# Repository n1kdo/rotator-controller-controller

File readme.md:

# Raspberry Pi Pico W IOT Antenna Rotator Controller Controller

This project uses a Raspberry Pi Pico W to internet-enable one or two antenna 
rotator controllers that have an RS-232 interface.  The software presents a web interface 
to the rotator, and also allows direct network control by N1MM+ and other software.

I used it for my Hy-Gain Ham IV rotator.  My Hy-Gain rotator control box has been modified to allow computer
control with the addition of a Ham Supply/Idiom Press *Rotor-EZ* module.  I further modified the rotator
control box to provide +5 Volts on Pin 1 (carrier detect) of the DE-9S RS-232 interface.  This allows the 
Raspberry Pi Pico W to rob power from the rotator control box.

See the [Documentation](documentation.md) for details.

There is very little external hardware required.  The most important other piece is a MAX3232 3.3 volt 
RS-232 level converter.  The MAX3232 is used to interface the 3.3 volt logic of the Raspberry Pi Pico W to
the RS-232 levels required by the antenna rotator control box.

## Installing MicroPython on your Pico-W

1. Download the latest stable build of [Pico W MicroPython](https://micropython.org/download/RPI_PICO_W/). 
   [This is the direct link](https://www.micropython.org/resources/firmware/RPI_PICO_W-20260824-v1.29.0.uf2).
2. Connect a micro-USB cable to your PC.  Hold down the white "BOOTSEL" button on the Pico-W, and insert the
   micro-USB cable into your Pico-W.
3. The Pico-W should appear as a USB storage device on your computer.  On mine, it shows up as "RPI-RP2 (F:)".
4. Copy/Paste the MicroPython .uf2 file to this drive.
5. Disconnect the Pico-W and prepare for the next step.

## Installing this software onto the Pico-W

The easiest way to get this software installed onto your Pico-W is to use the `loader.py` tool, also
provided in this repository.

1. Download Python 3 from https://www.python.org/downloads/ and install it.  Make sure to select "Add 
   Python 3 to Path."
2. Download the contents of this GitHub repository as a zip.  Use this URL: 
   `https://github.com/n1kdo/rotator-controller-controller/archive/refs/heads/master.zip`
3. Unpack that zip file somewhere. 
4. Open a command prompt.  (your choice.  Could be PowerShell, could be good ole CMD.)
5. From the command line, execute the following command: `pip install pyserial` -- this will install the Python 
   serial port support/
6. Change directory to where you unpacked the GitHub zip file, and then
   change directory to the `src/loader` directory.
7. From the command line, execute the following command: `python loader.py` -- this will install all the rotator
   controller-controller software onto the Pico-W.

If you want to experiment, you can use the open-source "Thonny" IDE to load the python source code and HTML files
onto the Pico W.  Unfortunately, Thonny cannot load the binary file `compass-background.png` image file into the
proper location, but this can be worked around by using the "upload" feature in the controller-controller software.

## What is all this stuff?

Important files:

* src/rotator/main.py -- the main Python application
* src/rotator/dcu1_rotator.py -- a Python module that queries and commands the rotator controller
* src/rotator/http_server.py -- a Python module that implements the web server
* src/rotator/morse_code.py -- a Python module that implements the morse code sender
* src/rotator/n1mm_udp.py -- a Python module that implements UDP send/receive to/from N1MM+
* src/rotator/content/rotator.html -- the rotator control web page
* src/rotator/content/setup.html -- the setup web page
* src/rotator/content/files.html -- the file upload/download web page
* src/rotator/data/config.json -- the configuration file.  automatically generated on first use if not present.

Other Stuff:

* src/loader/loader.py -- small Python application installs the six files above onto the Pico-W
* src/loader/pyboard.py -- patched pyboard library from Micropython. Patched to work on Pico-W.

Electronic Design Files:

* kicad/* -- Kicad 6 design files for schematic and PCB.

## Other projects using this technology

I used this same electronic design, and a lot of the same source code to make
the [KPA-500 IOT Thing](https://github.com/n1kdo/KPA500-remote), a web interface and 
KPA500-remote *host* for the Elecraft KPA-500 amplifier.

## Yes it works with N1MM+

See [Using the Rotator Controller-Controller with N1MM+](N1MM.md)

n1kdo 2026-09-21

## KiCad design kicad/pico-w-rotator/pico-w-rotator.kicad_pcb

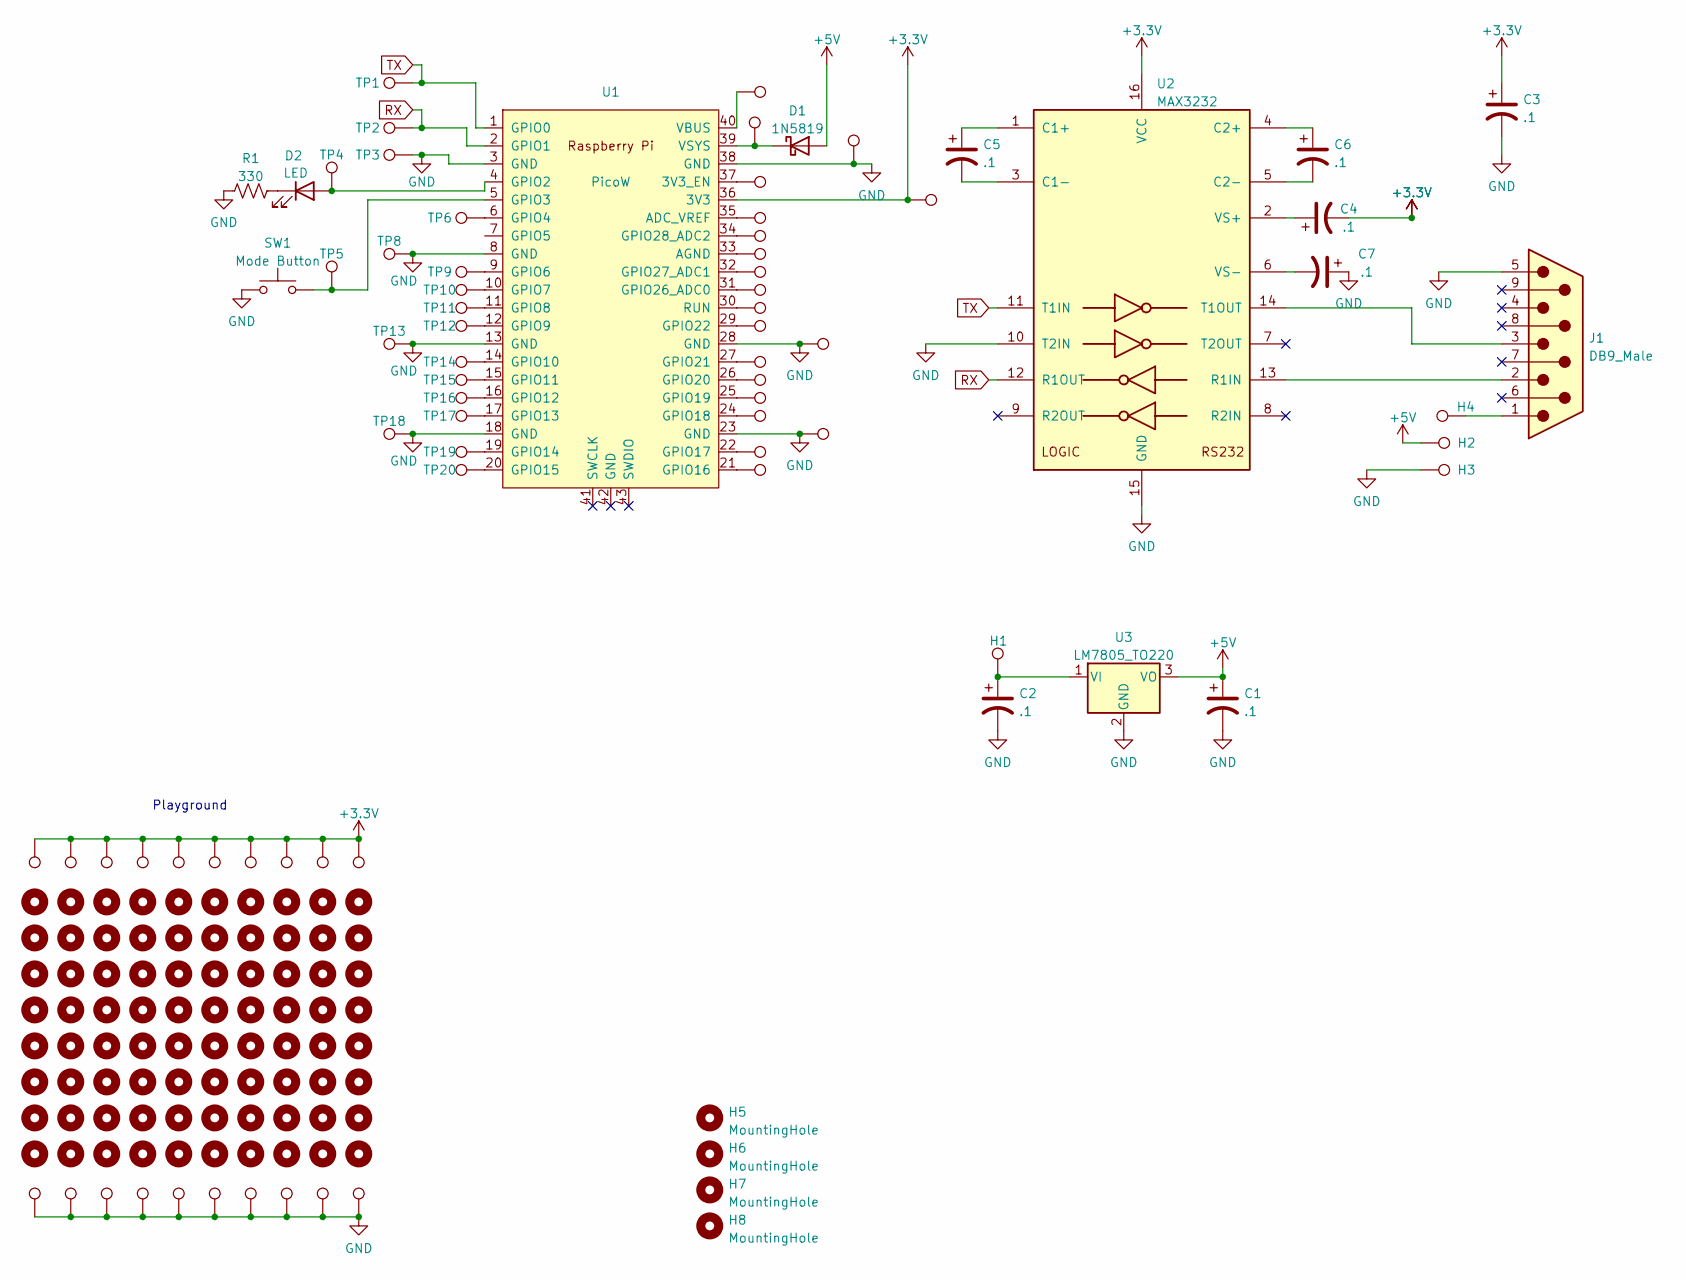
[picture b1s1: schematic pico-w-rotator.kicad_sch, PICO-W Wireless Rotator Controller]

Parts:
C1, C2, C3, C4, C5, C6, C7: .1; CP_Radial_Tantal_D4.5mm_P2.50mm; part T350A104M035AT
D1: 1N5819; D_DO-41_SOD81_P7.62mm_Horizontal
D2: LED; LED_D3.0mm
GH1, GH2, GH3, GH4, GH5, GH6, GH7, GH8, GH9, GH10, GH11, GH12, GH13, GH14, GH15, GH16, GH17, GH18, GH19, GH20, GH21, GH22, GH23, GH24, GH25, GH26, GH27, GH28, GH29, GH30, GH31, GH32, GH33, GH34, GH35, GH36, GH37, GH38, GH39, GH40, GH41, GH42, GH43, GH44, GH45, GH46, GH47, GH48, GH49, GH50, GH51, GH52, GH53, GH54, GH55, GH56, GH57, GH58, GH59, GH60, GH61, GH62, GH63, GH64, GH65, GH66, GH67, GH68, GH69, GH70, GH71, GH72, GH73, GH74, GH75, GH76, GH77, GH78, GH79, GH80, GH81, GH82, GH83, GH84, GH85, GH86, GH87, GH88, GH89, GH90, GH91, GH92, GH93, GH94, GH95, GH96, GH97, GH98, GH99, GH100: MountingHole; TestPoint_THTPad_D1.0mm_Drill0.5mm
H1, H3: 3; TestPoint_THTPad_D1.0mm_Drill0.5mm
H2: 2; TestPoint_THTPad_D1.0mm_Drill0.5mm
H4: 1; TestPoint_THTPad_D1.0mm_Drill0.5mm
H5, H6, H7, H8: MountingHole; MountingHole_3.5mm
J1: DB9_Male; DSUB-9_Male_Horizontal_P2.77x2.84mm_EdgePinOffset4.94mm_Hou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; part L717SDE09PA4CH4RC309
R1: 330; R_Axial_DIN0207_L6.3mm_D2.5mm_P7.62mm_Horizontal
SW1: Mode Button; GB215AHB; part GB215AH
TP1, TP2, TP3, TP4, TP5, TP6, TP8, TP9, TP10, TP11, TP12, TP13, TP14, TP15, TP16, TP17, TP18, TP19, TP20, TP21, TP22, TP23, TP24, TP25, TP26, TP27, TP28, TP29, TP30, TP31, TP32, TP33, TP34, TP35, TP36, TP37, TP38, TP39, TP40: TestPoint; TestPoint_THTPad_D1.0mm_Drill0.5mm
U1: PicoW; RPi_PicoW_SMD_TH
U2: MAX3232; DIP-16_W7.62mm_Socket
U3: LM7805_TO220; TO-220-3_Vertical

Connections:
+3.3V: C3.1, C4.2, GH1.1, GH11.1, GH21.1, GH31.1, GH41.1, GH51.1, GH61.1, GH71.1, GH81.1, GH91.1, TP36.1, U1.36 (3V3), U2.16 (VCC)
+5V: C1.1, D1.2 (A), H2.1, U3.3 (VO)
GND: C1.2, C2.2, C3.2, C7.1, GH10.1, GH20.1, GH30.1, GH40.1, GH50.1, GH60.1, GH70.1, GH80.1, GH90.1, GH100.1, H3.1, J1.5, R1.1, SW1.1, TP3.1, TP8.1, TP13.1, TP18.1, TP23.1, TP28.1, TP38.1, U1.3 (GND), U1.8 (GND), U1.13 (GND), U1.18 (GND), U1.23 (GND), U1.28 (GND), U1.38 (GND), U2.10 (T2IN), U2.15 (GND), U3.2 (GND)
unnamed: C2.1, H1.1, U3.1 (VI)
unnamed: C4.1, U2.2 (VS+)
unnamed: C5.1, U2.1 (C1+)
unnamed: C5.2, U2.3 (C1-)
unnamed: C6.1, U2.4 (C2+)
unnamed: C6.2, U2.5 (C2-)
unnamed: C7.2, U2.6 (VS-)
unnamed: D1.1 (K), TP39.1, U1.39 (VSYS)
unnamed: D2.1 (K), R1.2
unnamed: D2.2 (A), TP4.1, U1.4 (GPIO2)
unnamed: H4.1, J1.1
unnamed: J1.2, U2.13 (R1IN)
unnamed: J1.3, U2.14 (T1OUT)
unnamed: SW1.2, TP5.1, U1.5 (GPIO3)
unnamed: TP6.1, U1.6 (GPIO4)
unnamed 18: U1.7 (GPIO5); also elsewhere on the board
unnamed: TP9.1, U1.9 (GPIO6)
unnamed: TP10.1, U1.10 (GPIO7)
unnamed: TP11.1, U1.11 (GPIO8)
unnamed: TP12.1, U1.12 (GPIO9)
unnamed: TP14.1, U1.14 (GPIO10)
unnamed: TP15.1, U1.15 (GPIO11)
unnamed: TP16.1, U1.16 (GPIO12)
unnamed: TP17.1, U1.17 (GPIO13)
unnamed: TP19.1, U1.19 (GPIO14)
unnamed: TP20.1, U1.20 (GPIO15)
unnamed: TP21.1, U1.21 (GPIO16)
unnamed: TP22.1, U1.22 (GPIO17)
unnamed: TP24.1, U1.24 (GPIO18)
unnamed: TP25.1, U1.25 (GPIO19)
unnamed: TP26.1, U1.26 (GPIO20)
unnamed: TP27.1, U1.27 (GPIO21)
unnamed: TP29.1, U1.29 (GPIO22)
unnamed: TP30.1, U1.30 (RUN)
unnamed: TP31.1, U1.31 (GPIO26_ADC0)
unnamed: TP32.1, U1.32 (GPIO27_ADC1)
unnamed: TP33.1, U1.33 (AGND)
unnamed: TP34.1, U1.34 (GPIO28_ADC2)
unnamed: TP35.1, U1.35 (ADC_VREF)
unnamed: TP37.1, U1.37 (3V3_EN)
unnamed: TP40.1, U1.40 (VBUS)
RX: TP2.1, U1.2 (GPIO1), U2.12 (R1OUT)
TX: TP1.1, U1.1 (GPIO0), U2.11 (T1IN)

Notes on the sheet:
Playground

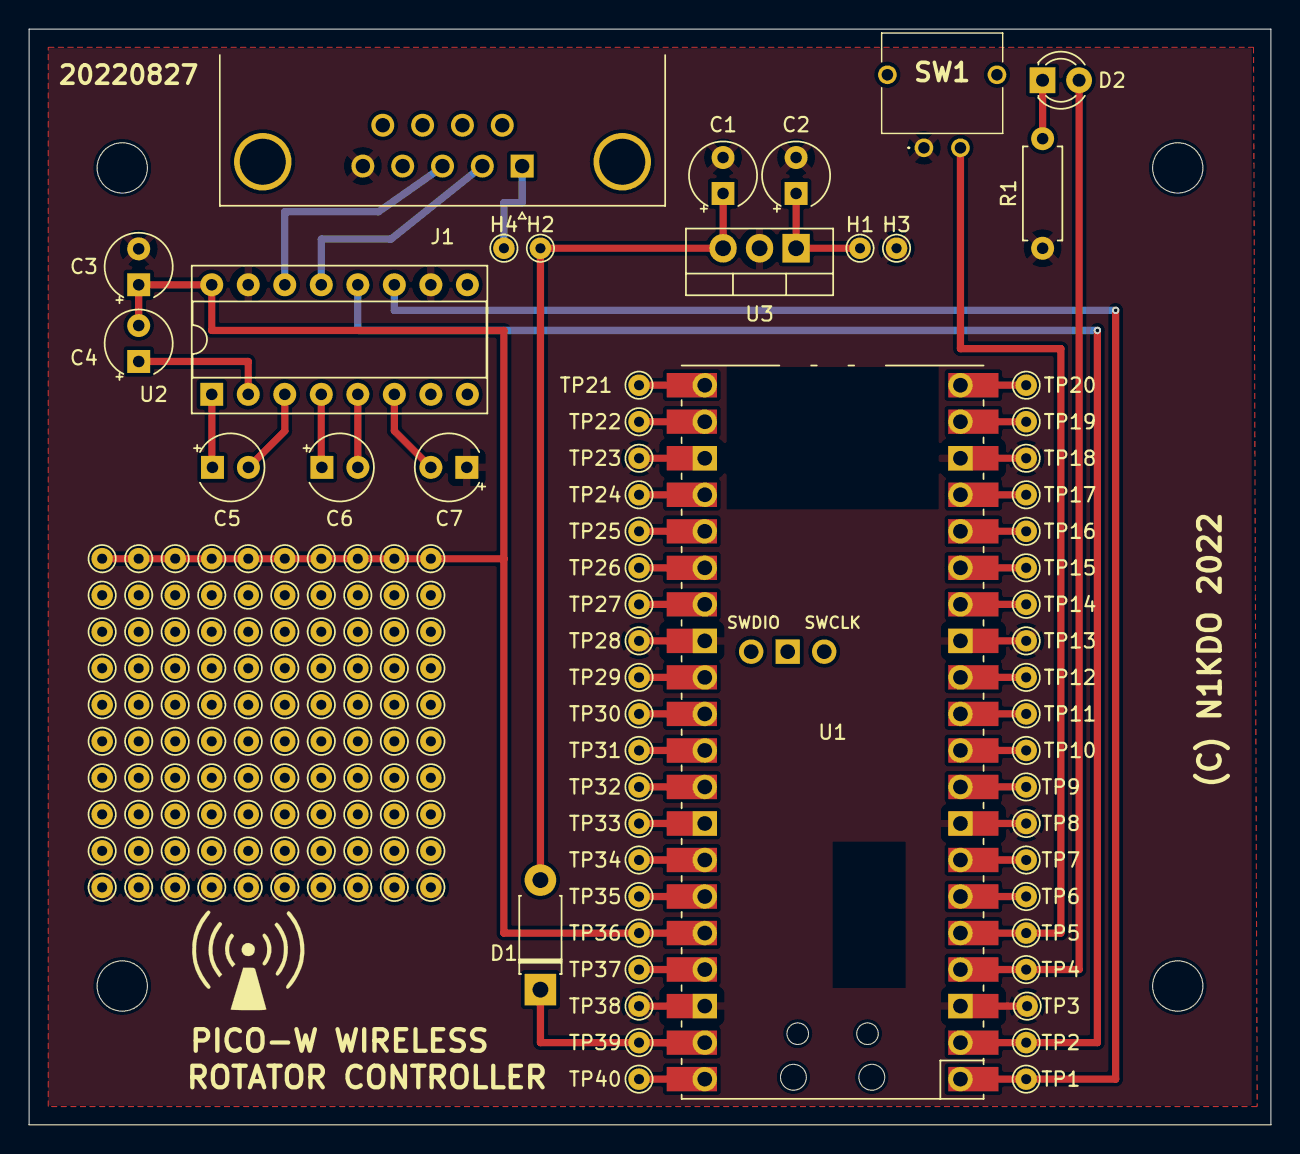
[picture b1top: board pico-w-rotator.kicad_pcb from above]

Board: 2 copper layers, 86.4 x 76.2 mm, 164 parts (0 on the bottom side), 46 nets.

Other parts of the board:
G1: LOGO; non-ionizing-bigger
TP7: TestPoint; TestPoint_THTPad_D1.5mm_Drill0.7mm

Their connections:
unnamed 18: TP7.1; also elsewhere on the board

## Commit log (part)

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2022-08-06 ooh working.
2022-08-06 ooh working still
2022-08-06 working even better now.
2022-08-06 copyright notice added.
    BSD 2-clause
2022-08-06 some documentation
2022-08-09 async web service
2022-08-10 update update
2022-08-12 add refresh button, now has telnet client
    so far only tested with LP-Rotor
2022-08-13 change refresh UI to radio buttons
    general cleanups
2022-08-20 adding configuration
    this commit adds:
    * access point mode, insecure
    * /config endpoint, GET works, POST not yet tested.
    * config.json file has ssid, secret, web port, tcp port
    general cleanups
2022-08-20 adding configuration
    this commit adds:
    setup.html form
2022-08-21 added hardware!
    moved some stuff around.
2022-08-24 config stuff.
2022-08-24 styling
2022-08-25 image background!
2022-08-26 memory usage
2022-08-26 file right-sizing.
2022-08-27 pcb measured, checked
    sent out to oshpark!
2022-08-28 pcb measured, checked
    sent out to oshpark!
    schem changed, sanity
2022-08-28 serve content in 4k blocks to save memory.
2022-09-05 added step file data for better 3d experience
2022-09-05 file uploading to master
2022-09-05 remove obsoletes
2022-09-06 fix strings, add some api methods, etc
2022-09-10 make rename work on micropython
2022-09-11 reorganized files. send IP in Morse on LED.
2022-09-11 improvements to loader, will restart device now.
2022-09-18 improvements to loader, will detect pico-w now.
    updated doc to some degree
2022-09-18 adding images & etc.
2022-10-29 moved morse sender into its own co-routine.
2022-11-27 some refactoring
2022-12-27 add license
2023-01-14 compartmentalize functionality for maintainability.
2023-01-14 make rotor control code more portable
    by using SerialPort class.
2023-01-14 suppress warning
2023-01-14 static analyzer fixes, typos.
2023-01-14 make serial connection to rotor more robust.
2023-04-08 update readme, update favico
2023-04-29 code cleanups
2023-04-29 remove annoying
2023-04-29 remove more annoying pylint warnings
2023-04-29 mode code cleanups
2023-04-29 still more code cleanups
2023-04-29 yet still more code cleanups
2023-04-29 yet still even more code cleanups
2023-04-29 yet even still even more code cleanups
2023-04-29 yet even still another commit with even more code cleanups
2023-05-27 better 404 message.
    use primitive rotor control for DCU-3
2023-05-28 improve error handling
2023-06-03 add N1MM+ broadcasts send/receive direction
2023-06-03 set reasonable defaults if config is not found
2023-06-03 bugfix bad element id name
2023-08-10 added documentation.
2023-08-13 readme cleanup
2024-01-18 add remove file support, it was missing.
2024-01-20 fix upload support, remove support
2025-06-23 use latest loader.py, pyboard.py
2025-06-23 add logging, mostly.
2025-06-23 latest http_server.py
2025-06-23 use picow_network.py pull out network into its own module
2025-06-23 improve logging
2025-06-24 remove todo
2025-06-24 wordwrap reasonably
2025-06-25 add N1MM interfacing instructions.
2025-06-25 link to N1MM interfacing instructions.
2025-06-25 add development tool scripts
2025-07-07 reset access point mode on save
2025-07-07 clean up is_connected()
2025-07-07 modernize
2025-07-07 turn off debug
2025-07-07 bump version number
2025-07-28 clean up imports
2025-07-28 mergeathon
2025-07-28 adjust log messages
2025-07-28 clean up 'connected' logic
2025-07-28 remove duplicate get_message function
2025-08-16 Potential fix for code scanning alert no. 1: Workflow does not contain permissions
2025-12-25 add requirements.txt
2025-12-25 latest loader.py
2025-12-26 latest http_server and pico_network
2025-12-29 update some common code.
2026-01-01 latest pyboard.py
2026-01-01 update to latest common code.
2026-03-15 latest serialport.py
2026-03-17 support two rotors on the Pico-W Dual Serial card
2026-03-17 remove TODO, set logging level to INFO
2026-06-13 fix rotor 2 validation
2026-06-14 experiment
2026-06-15 experimenting with scanning APs to populate list

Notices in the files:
kicad/pico-w-rotator/pico-w-rotator.kicad_pcb:
Copyright 2022, J. B. Otterson N1KDO.
kicad/pico-w-rotator/pico-w-rotator.kicad_sch:
Copyright (C) 2022 J. B. Otterson N1KDO
